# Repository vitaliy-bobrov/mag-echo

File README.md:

# Mag Echo

Mag Echo delay + modulation based on Keeley Mag Echo.

The repository contains KiCad source files: schematic, PCB, BOM.

## Schematic

## PCB (3D preview)

## Interactive BOM

👉 [BOM](https://vitaliy-bobrov.github.io/mag-echo/)

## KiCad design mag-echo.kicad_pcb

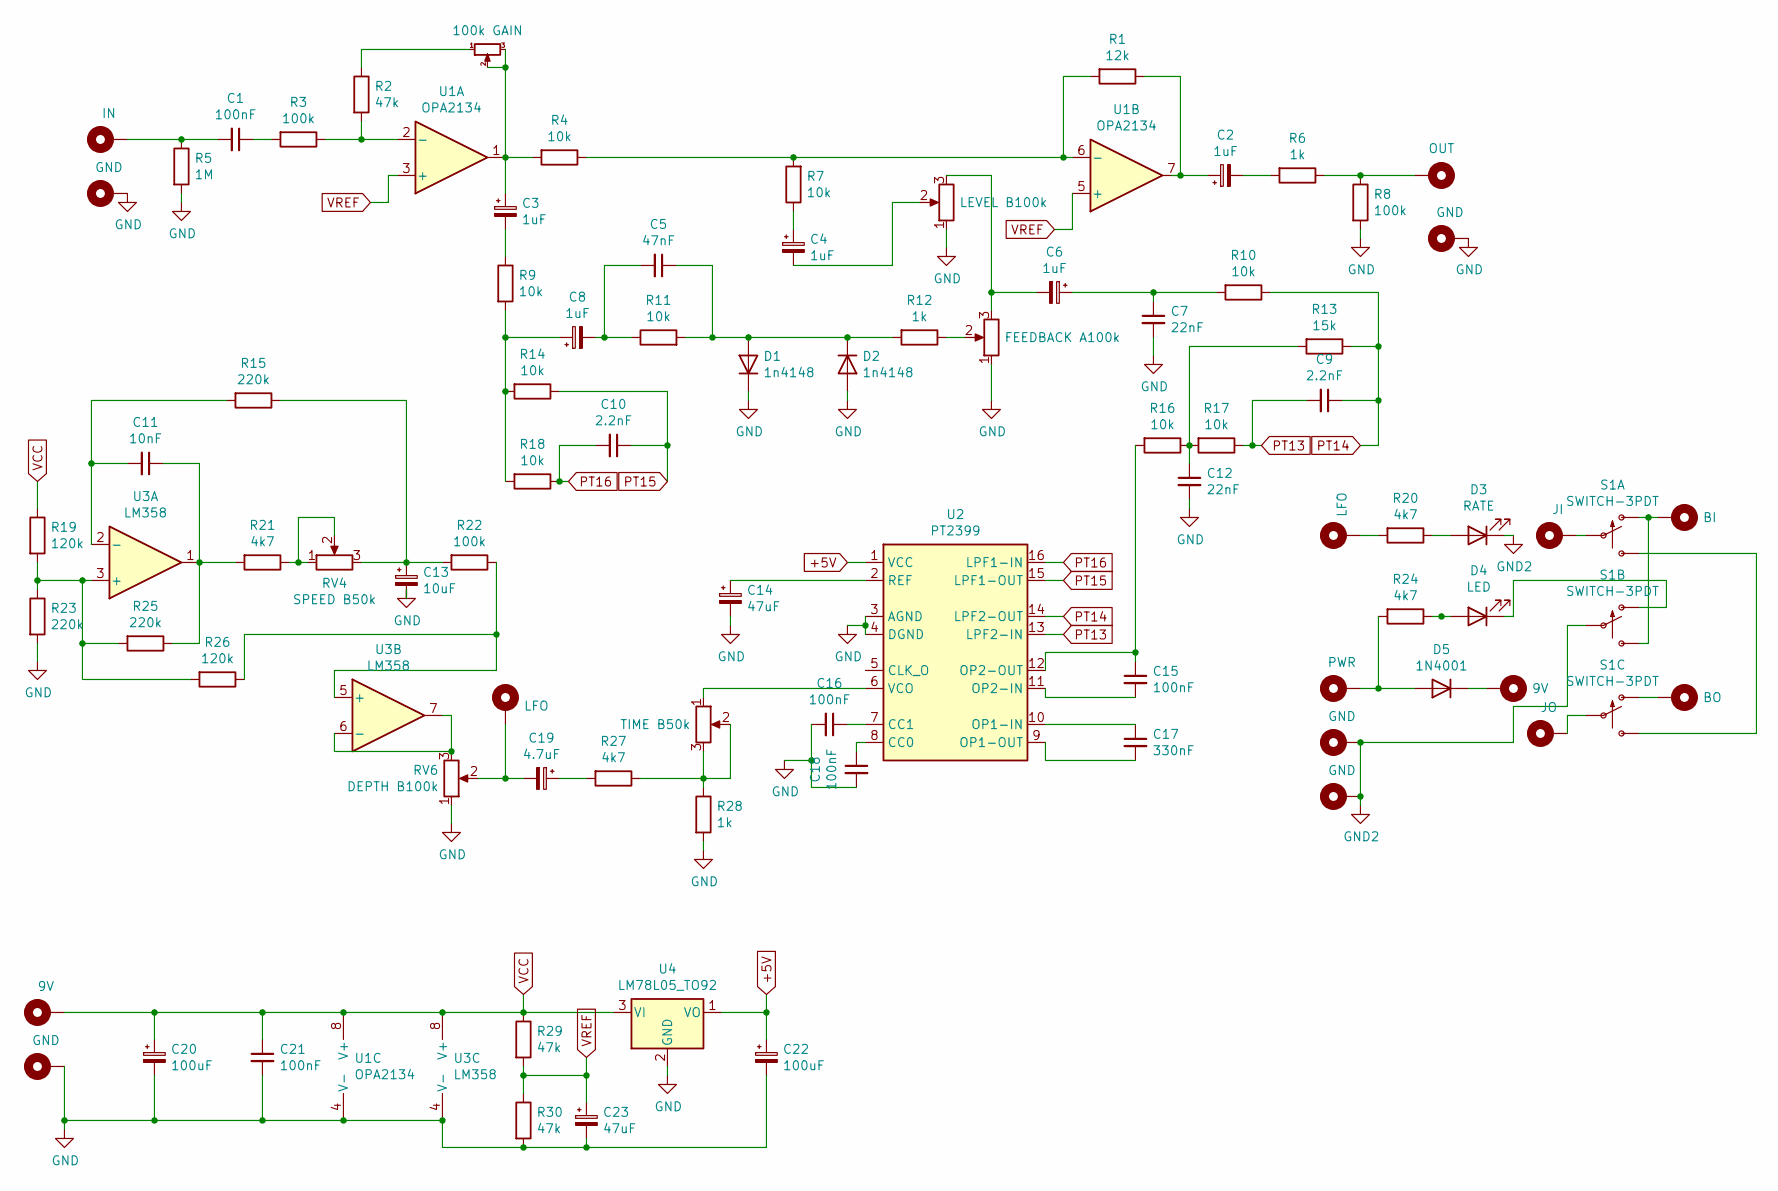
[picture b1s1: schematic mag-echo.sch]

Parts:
C1, C15, C16, C18, C21: 100nF; 0.2%22.SML
C2, C3, C4, C6, C8: 1uF; 0503
C5: 47nF; 0.2%22.SML
C7, C12: 22nF; 0.2%22.SML
C9, C10: 2.2nF; 0.2%22.SML
C11: 10nF; 0.2%22.SML
C13: 10uF; 0503
C14, C23: 47uF; 0632
C17: 330nF; 0.2%22.SML
C19: 4.7uF; 0503
C20, C22: 100uF; 0632
D1, D2: 1n4148; DO35-3
D3: RATE; LED_D3.0mm
D4: LED; LED_D3.0mm
D5: 1N4001; D_DO-41_SOD81_P10.16mm_Horizontal
H1: IN; PAD1
H2: OUT; PAD1
H3, H4, H13, H14, H16: GND; PAD1
H5: BI; PAD1
H6, H11: LFO; PAD1
H7: JI; PAD1
H8: PWR; PAD1
H9, H15: 9V; PAD1
H10: BO; PAD1
H12: JO; PAD1
R1: 12k; 0.3%22.A
R2, R29, R30: 47k; 0.3%22.A
R3, R8, R22: 100k; 0.3%22.A
R4, R7, R9, R10, R11, R14, R16, R17, R18: 10k; 0.3%22.A
R5: 1M; 0.3%22.A
R6, R12, R28: 1k; 0.3%22.A
R13: 15k; 0.3%22.A
R15, R23, R25: 220k; 0.3%22.A
R19, R26: 120k; 0.3%22.A
R20, R21, R24, R27: 4k7; 0.3%22.A
RV1: 100k GAIN; TRIM1
RV2: LEVEL B100k; 16MM_B.MOUNT
RV3: FEEDBACK A100k; 16MM_B.MOUNT
RV4: SPEED B50k; 16MM_B.MOUNT
RV5: TIME B50k; 16MM_B.MOUNT
RV6: DEPTH B100k; 16MM_B.MOUNT
S1: SWITCH-3PDT; 3PDT.LUGS.SPF
U1: OPA2134; DIP-8_W7.62mm_Socket
U2: PT2399; DIP-16_W7.62mm_Socket
U3: LM358; DIP-8_W7.62mm_Socket
U4: LM78L05_TO92; TO-92_Inline

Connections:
+5V: C22.1, U2.1 (VCC), U4.1 (VO)
GND: C7.2, C12.2, C13.2, C14.2, C16.2, C18.2, C20.2, C21.2, C22.2, C23.2, D1.1 (K), D2.2 (A), H3.1, H4.1, H16.1, R5.2, R8.2, R23.2, R28.2, R30.2, RV2.1, RV3.1, RV6.1, U1.4 (V-), U2.3 (AGND), U2.4 (DGND), U3.4 (V-), U4.2 (GND)
GND2: D3.1 (K), H13.1, H14.1, S1.P$5
unnamed: C1.1, R3.2
unnamed: C1.2, H1.1, R5.1
unnamed: C2.1, R1.1, U1.7
unnamed: C2.2, R6.2
unnamed: C3.1, R4.2, RV1.2, RV1.3, U1.1
unnamed: C3.2, R9.1
unnamed: C4.1, R7.1
unnamed: C4.2, RV2.2
unnamed: C5.1, D1.2 (A), D2.1 (K), R11.2, R12.2
unnamed: C5.2, C8.2, R11.1
unnamed: C6.1, C7.1, R10.2
unnamed: C6.2, RV2.3, RV3.3
unnamed: C8.1, R9.2, R14.2, R18.2
unnamed: C11.1, R21.2, R25.1, U3.1
unnamed: C11.2, R15.2, U3.2 (-)
unnamed: C12.1, R13.2, R16.1, R17.2
unnamed: C13.1, R15.1, R22.2, RV4.3
unnamed: C14.1, U2.2 (REF)
unnamed: C15.1, R16.2, U2.12 (OP2-OUT)
unnamed: C15.2, U2.11 (OP2-IN)
unnamed: C16.1, U2.7 (CC1)
unnamed: C17.1, U2.10 (OP1-IN)
unnamed: C17.2, U2.9 (OP1-OUT)
unnamed: C18.1, U2.8 (CC0)
unnamed: C19.1, R27.2
unnamed: C19.2, H11.1, RV6.2
unnamed: D3.2 (A), R20.1
unnamed: D4.1 (K), S1.P$4 (O)
unnamed: D4.2 (A), R24.1
unnamed: D5.1 (K), H9.1
unnamed: D5.2 (A), H8.1, R24.2
unnamed: H2.1, R6.1, R8.1
unnamed: H5.1, S1.P$1 (O), S1.P$6 (S)
unnamed: H6.1, R20.2
unnamed: H7.1, S1.P$2
unnamed: H10.1, S1.P$7 (O)
unnamed: H12.1, S1.P$8
unnamed: R1.2, R4.1, R7.2, U1.6 (-)
unnamed: R2.1, RV1.1
unnamed: R2.2, R3.1, U1.2 (-)
unnamed: R12.1, RV3.2
unnamed: R19.2, R23.1, R25.2, R26.2, U3.3 (+)
unnamed: R21.1, RV4.1, RV4.2
unnamed: R22.1, R26.1, U3.5 (+)
unnamed: R27.1, R28.1, RV5.2, RV5.3
unnamed: RV5.1, U2.6 (VCO)
unnamed: RV6.3, U3.6 (-), U3.7
unnamed: S1.P$3 (S), S1.P$9 (S)
PT13: C9.2, R17.1, U2.13 (LPF2-IN)
PT14: C9.1, R10.1, R13.1, U2.14 (LPF2-OUT)
PT15: C10.1, R14.1, U2.15 (LPF1-OUT)
PT16: C10.2, R18.1, U2.16 (LPF1-IN)
VCC: C20.1, C21.1, H15.1, R19.1, R29.1, U1.8 (V+), U3.8 (V+), U4.3 (VI)
VREF: C23.1, R29.2, R30.1, U1.3 (+), U1.5 (+)

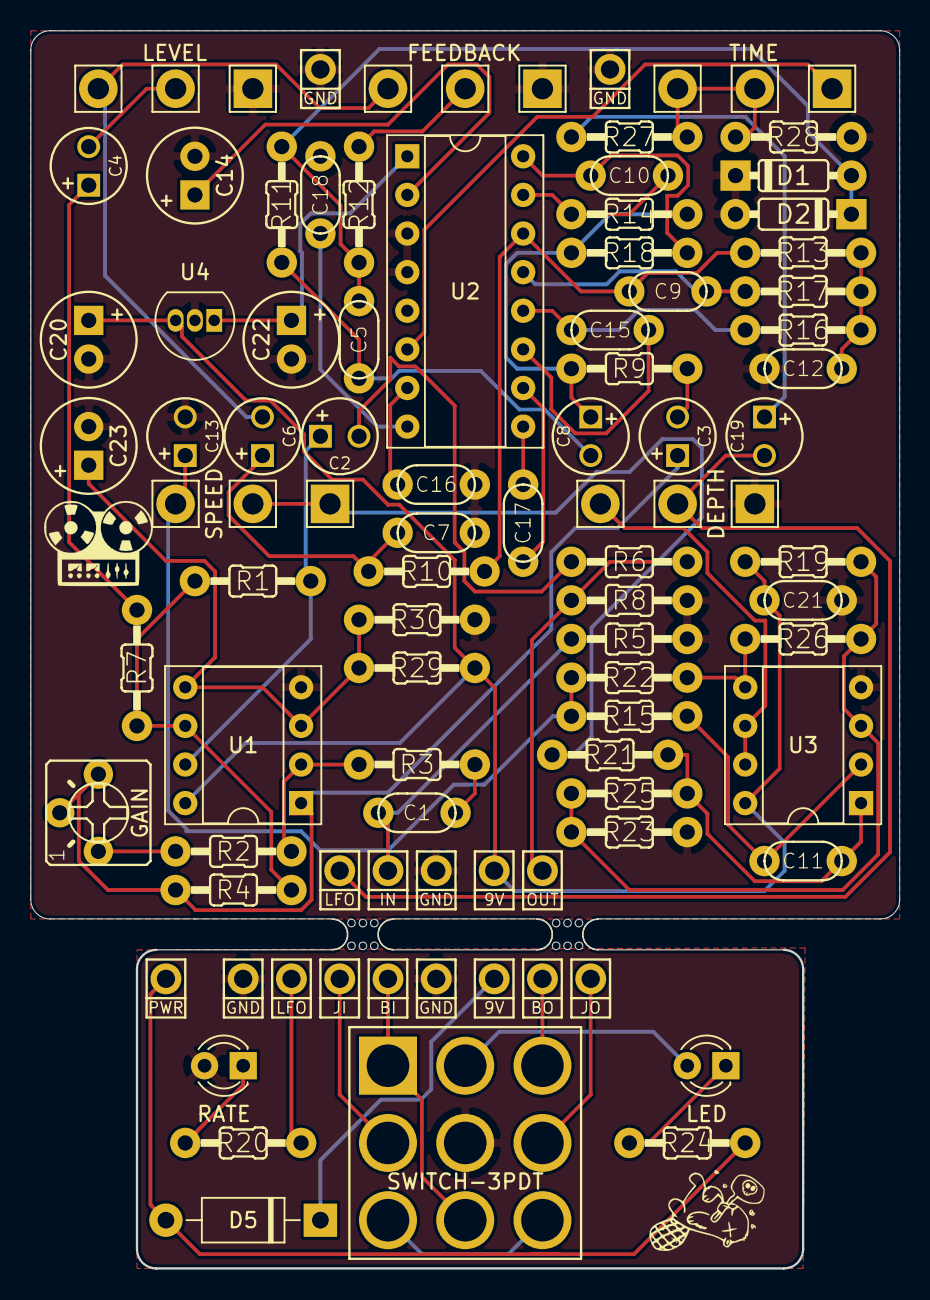
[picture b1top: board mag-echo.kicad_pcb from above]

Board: 2 copper layers, 57.1 x 81.4 mm, 90 parts (0 on the bottom side), 57 nets.

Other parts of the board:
JOUT4, JOUT4#2: LUMBURG_DRILL
Ref**: Val**; DC_TOP
mouse-bite-2mm-slot, mouse-bite-2mm-slot#2: VAL**; mouse-bite-2mm-slot

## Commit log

2020-10-21 v1.0
